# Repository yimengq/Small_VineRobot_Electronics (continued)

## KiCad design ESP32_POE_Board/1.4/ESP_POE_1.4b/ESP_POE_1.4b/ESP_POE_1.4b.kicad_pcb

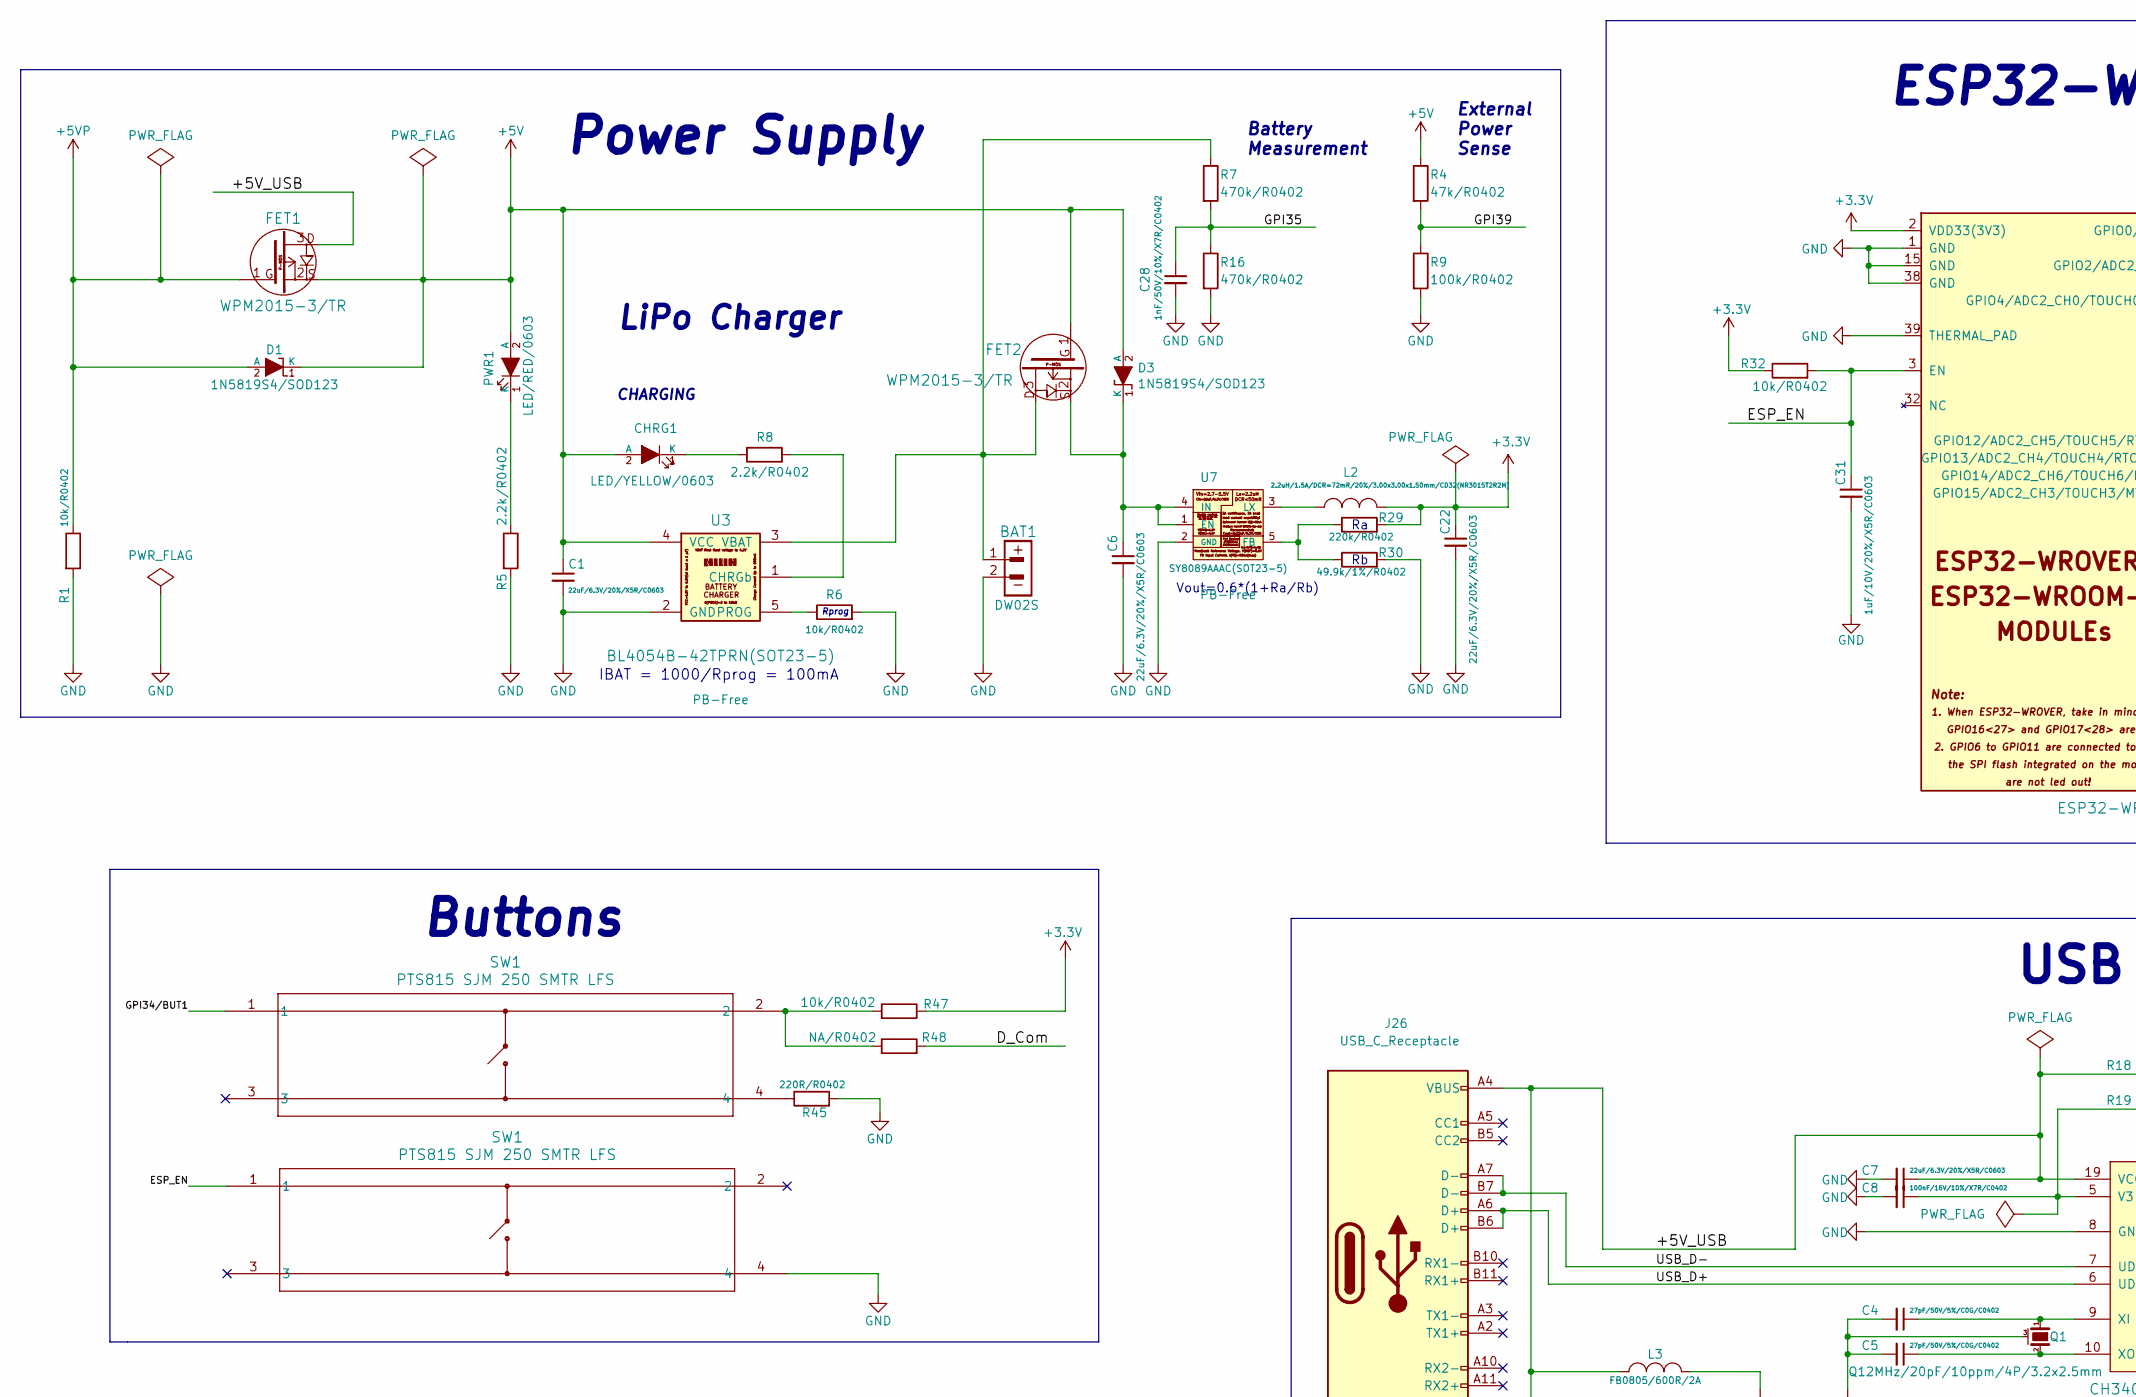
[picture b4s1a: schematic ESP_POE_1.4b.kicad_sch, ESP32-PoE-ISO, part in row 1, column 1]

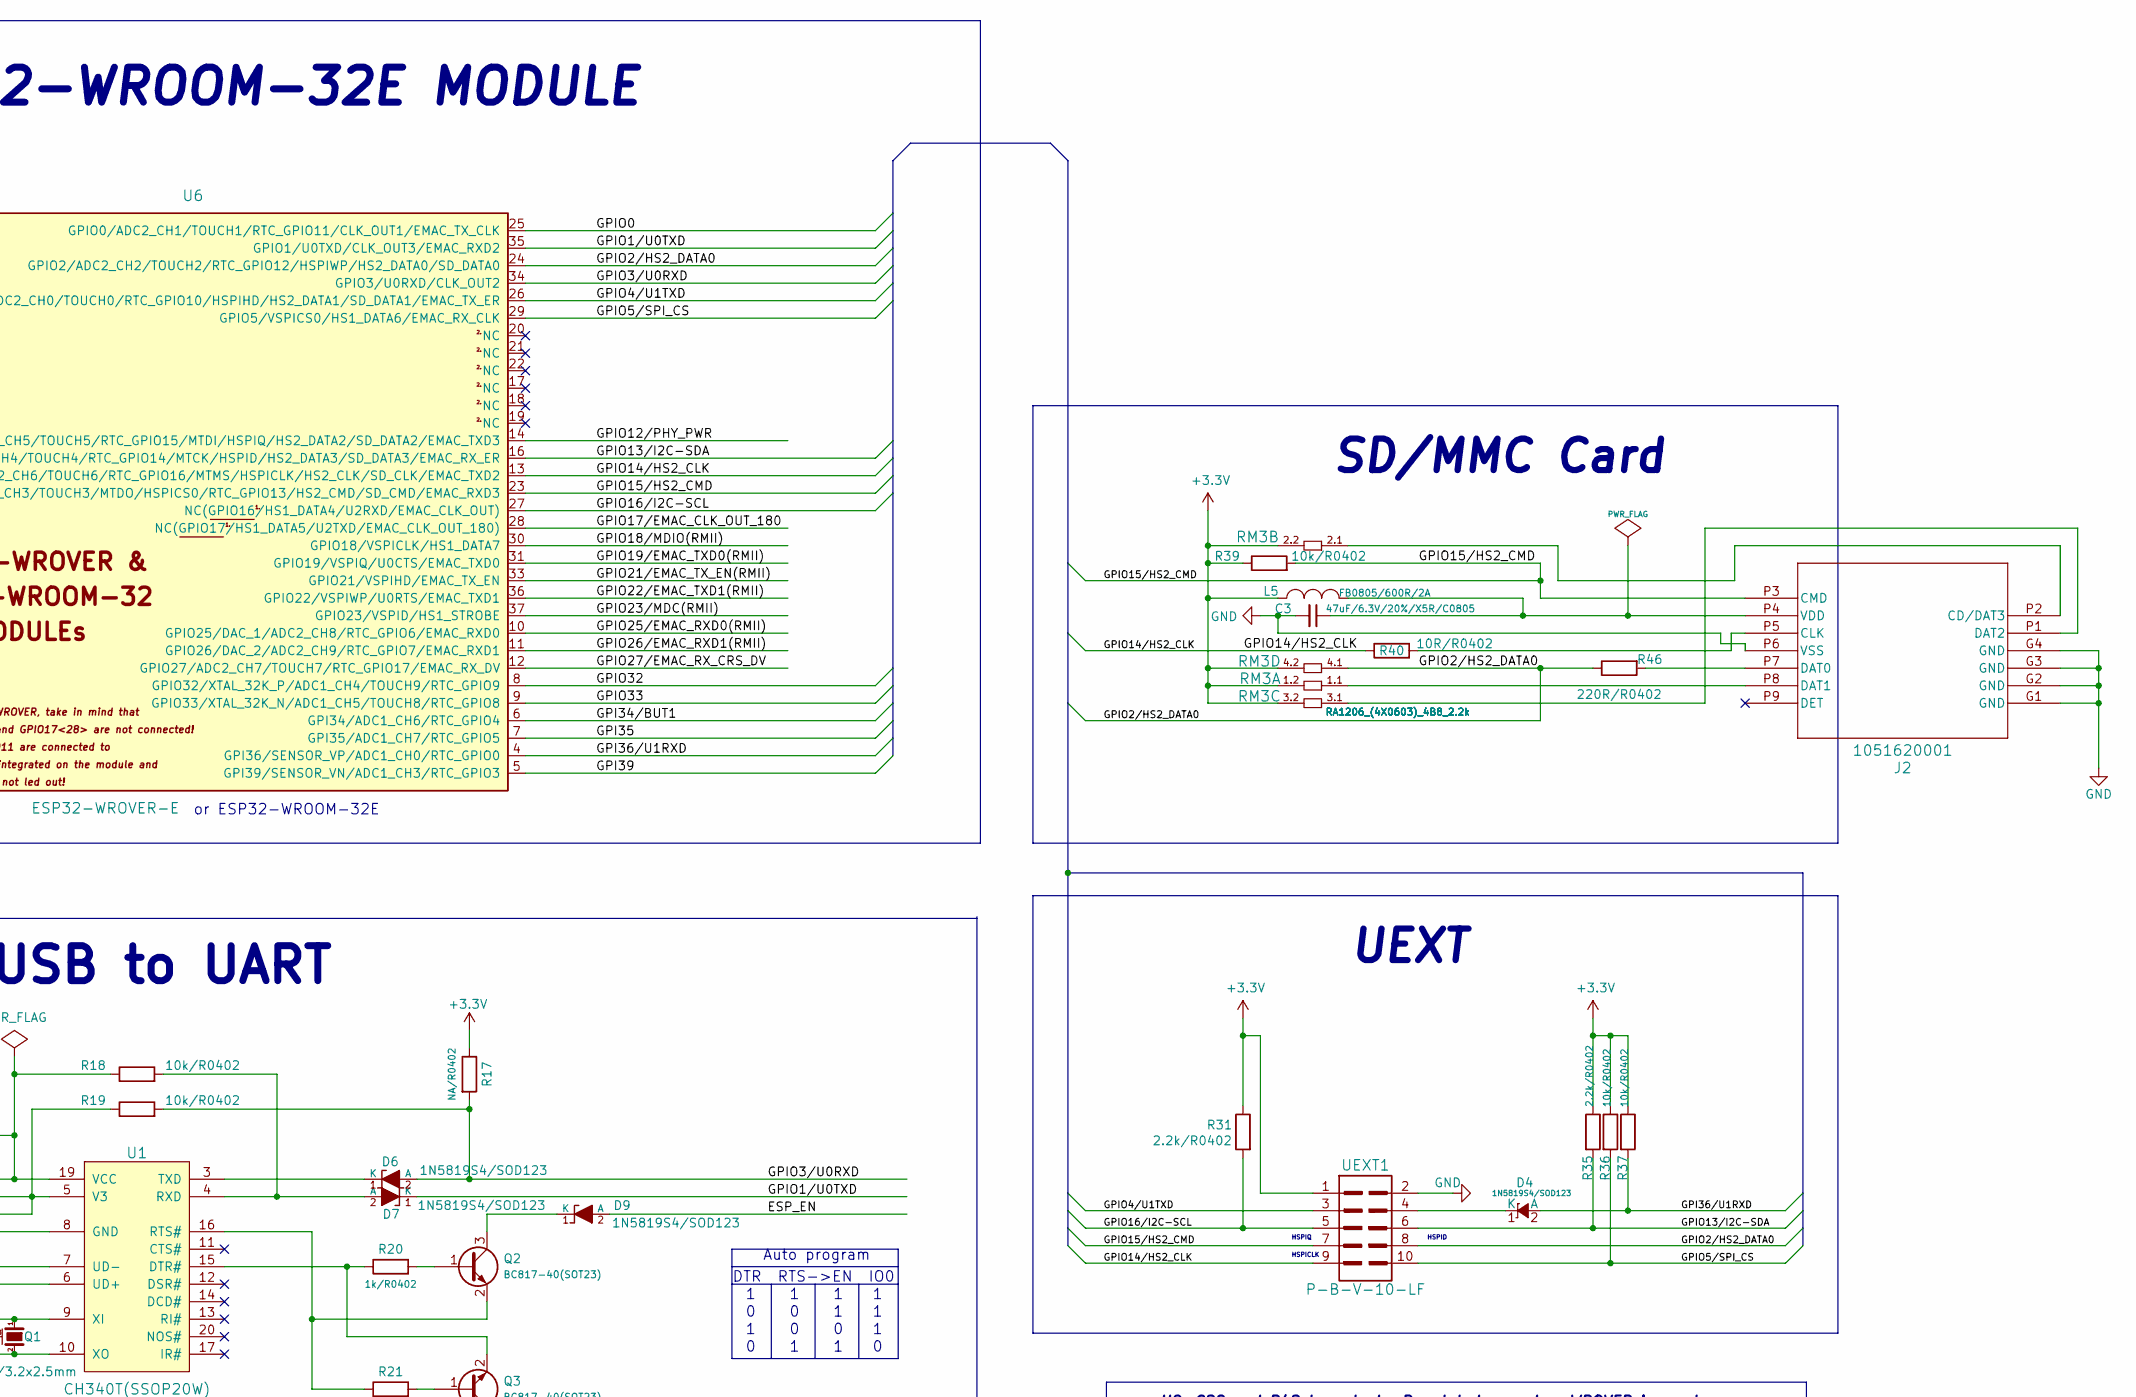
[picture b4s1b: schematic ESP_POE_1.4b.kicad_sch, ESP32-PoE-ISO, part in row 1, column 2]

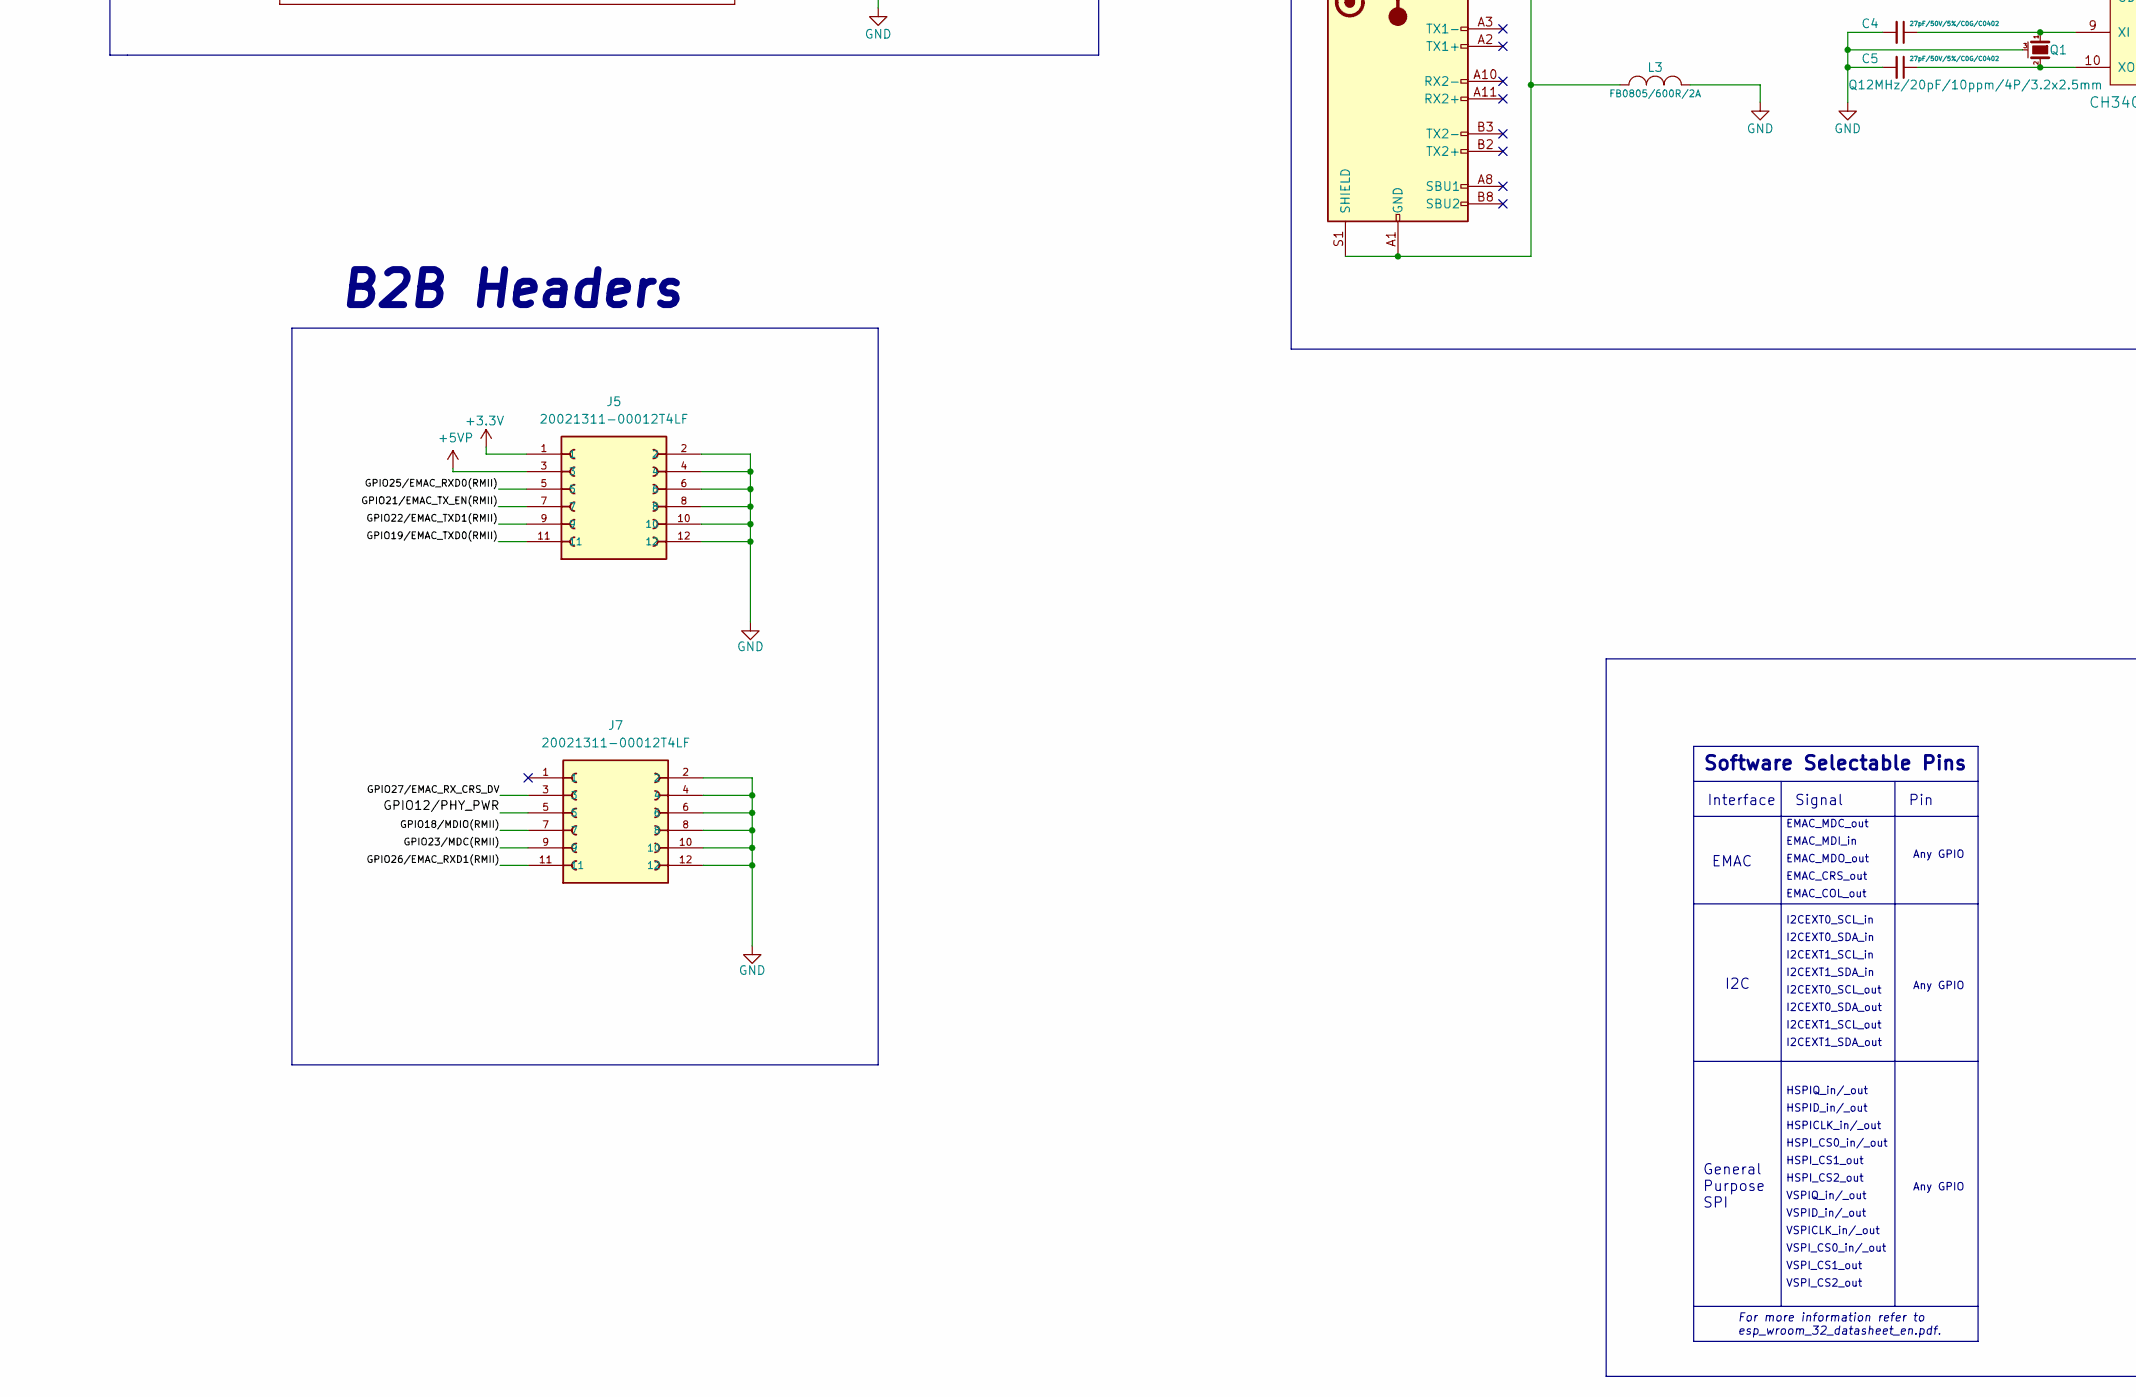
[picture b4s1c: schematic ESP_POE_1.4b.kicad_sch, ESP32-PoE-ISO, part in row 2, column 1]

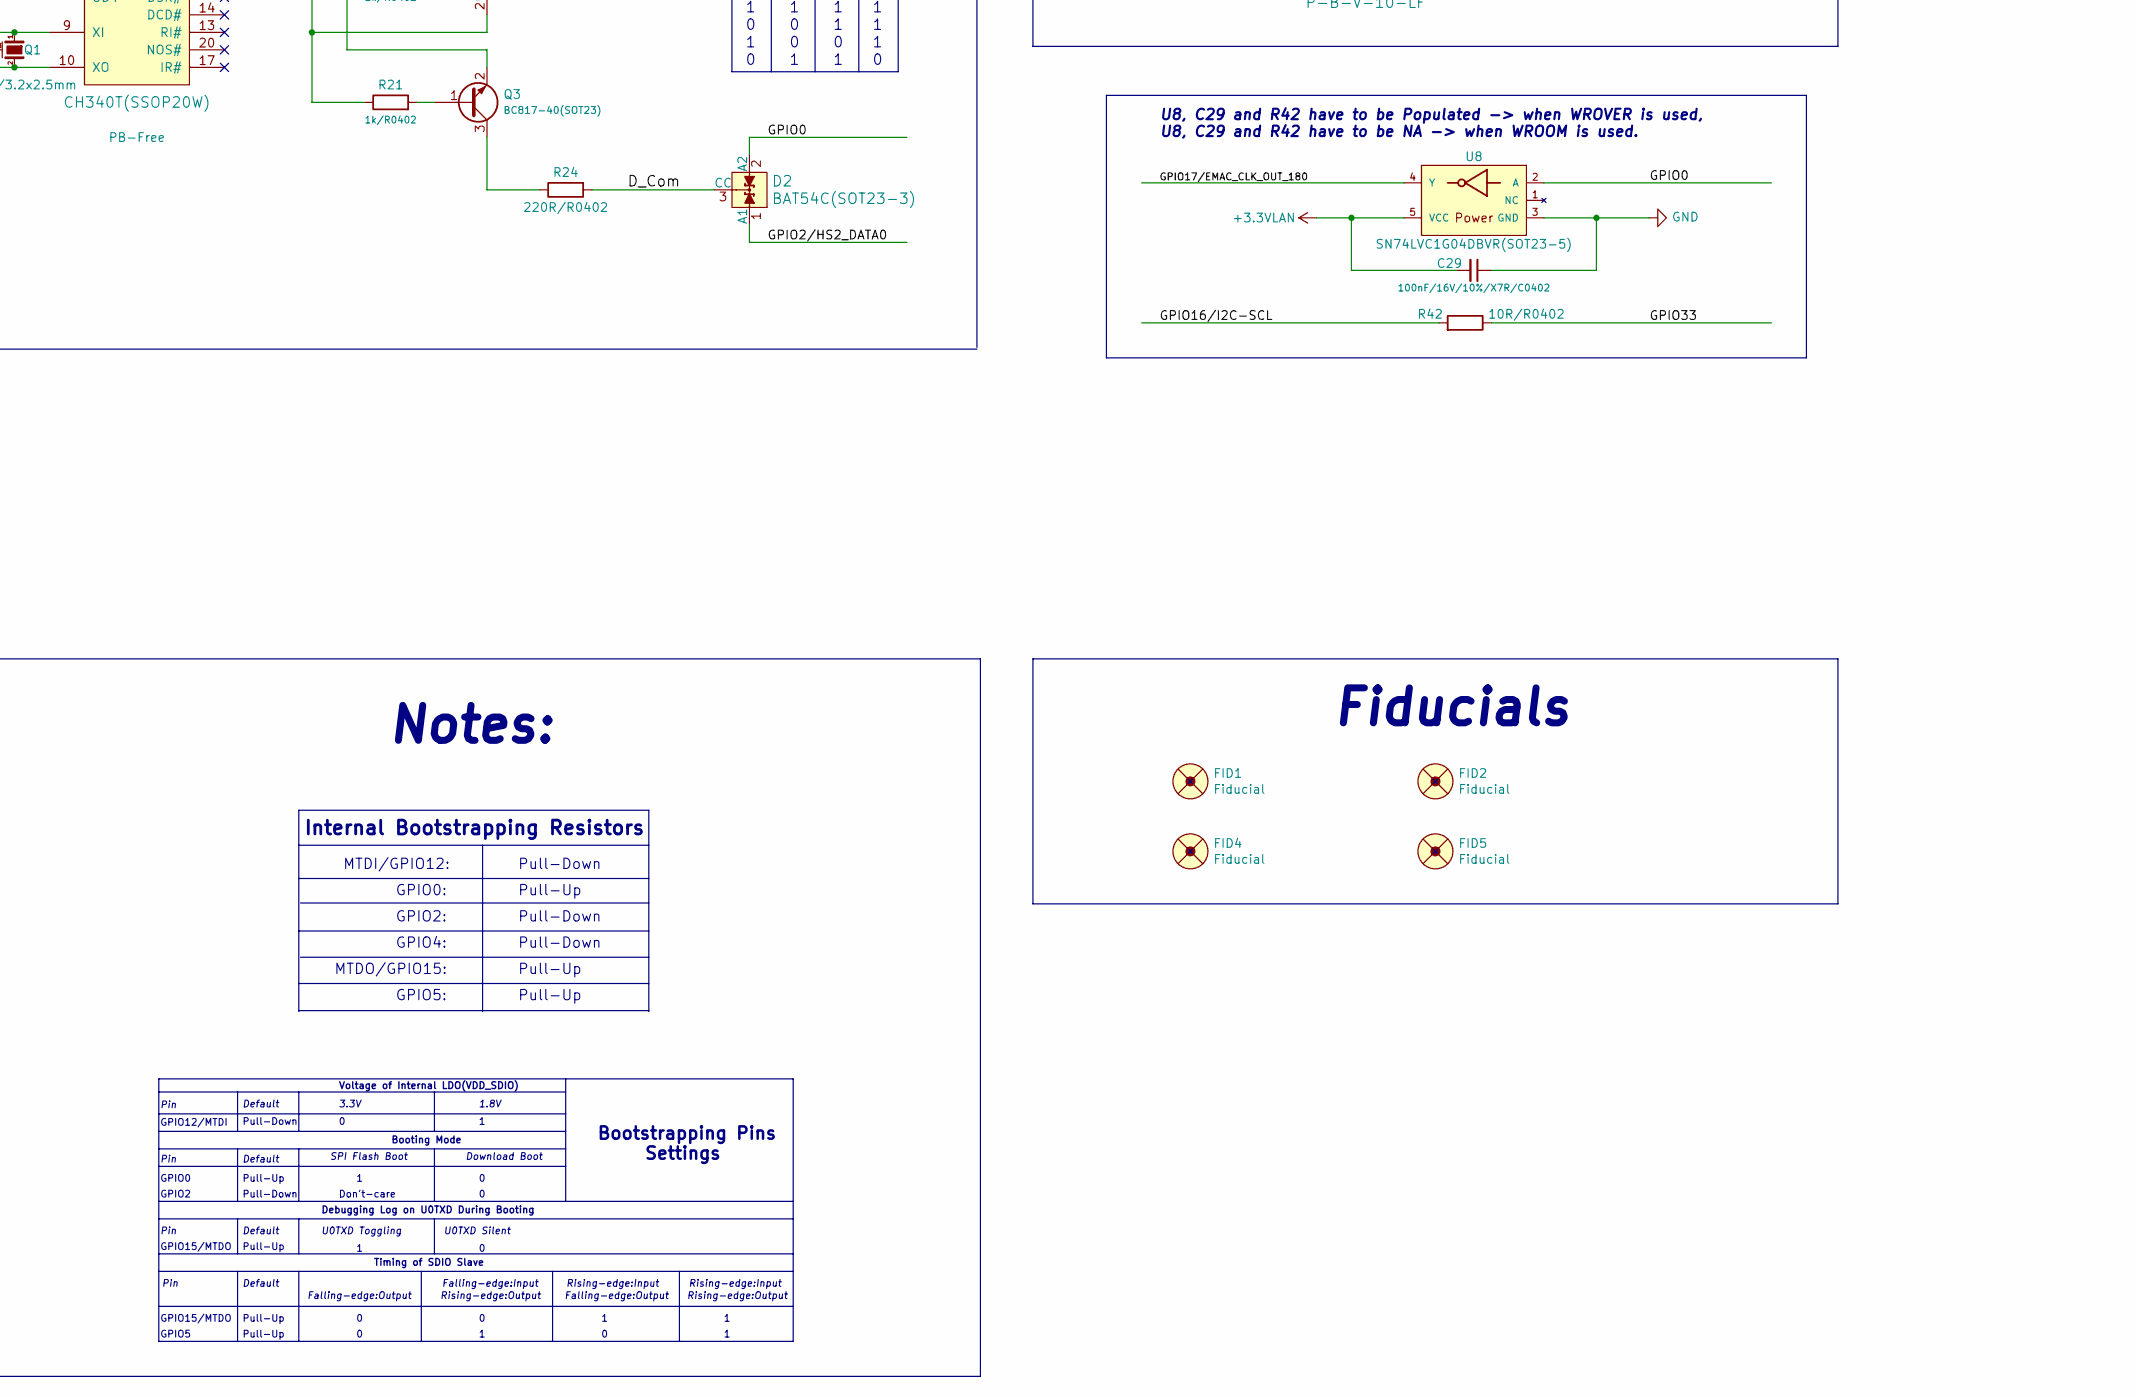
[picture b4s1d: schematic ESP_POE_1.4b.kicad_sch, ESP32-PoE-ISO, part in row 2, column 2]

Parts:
BAT1: DW02S; LIPO_BAT_VERTICAL_DW02S; Mfr P/N DF02S
C1, C6, C7, C22: 22uF/6.3V/20%/X5R/C0603; C_0603_5MIL_DWS; Mfr P/N CL10A226MQ8NRNC
C3: 47uF/6.3V/20%/X5R/C0805; C_0805_5MIL_DWS; Mfr P/N CL21A476MQYNNNE
C4, C5: 27pF/50V/5%/C0G/C0402; C_0402_5MIL_DWS; Mfr P/N CC0402FRNPO9BN270
C8, C29: 100nF/16V/10%/X7R/C0402; C_0402_5MIL_DWS; Mfr P/N CC0402KRX7R7BB104
C28: 1nF/50V/10%/X7R/C0402; C_0402_5MIL_DWS; Mfr P/N CC0402KRX7R9BB102
C31: 1uF/10V/20%/X5R/C0603; C_0603_5MIL_DWS; Mfr P/N CL10B105KP8NNNC
CHRG1: LED/YELLOW/0603; LED_0603_KA; Mfr P/N A-SP192GW1D-D20-4T
D1, D3, D4, D6, D7, D9: 1N5819S4/SOD123; SOD-123_1C-2A_KA; Mfr P/N 1N5819W S4
D2: BAT54C(SOT23-3); SOT23-3; Mfr P/N BAT54C
FET1, FET2: WPM2015-3/TR; SOT23; Mfr P/N WPM2015-3/TR
FID1, FID2, FID4, FID5: Fiducial; Fiducial1x3
J2: 1051620001; 105162-0001_MOL
J5, J7: 20021311-00012T4LF; AMPHENOL_20021311-00012T4LF; Mfr P/N 20021311-00012T4LF
J26: USB_C_Receptacle; USB_C_Receptacle_Molex_105450-0101-L; Mfr P/N 1054500101
L2: 2.2uH/1.5A/DCR=72mR/20%/3.00x3.00x1.50mm/CD32(NR3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; CD32; Mfr P/N ANR3015T2R2M
L3, L5: FB0805/600R/2A; L_0805_5MIL_DWS; Mfr P/N BLM21SP601SZ1D
PWR1: LED/RED/0603; LED_0603_KA; Mfr P/N A-SP194BR5C-C01-3T
Q1: Q12MHz/20pF/10ppm/4P/3.2x2.5mm; TSX-3.2x2.5mm_GND(3); Mfr P/N SX3B12.000F2010F30
Q2, Q3: BC817-40(SOT23); SOT23; Mfr P/N BC817-40,215
R1, R6, R18, R19, R32, R36, R37, R39: 10k/R0402; R_0402_5MIL_DWS; Mfr P/N RC0402FR-0710KL
R4: 47k/R0402; R_0402_5MIL_DWS; Mfr P/N AC0402JR-0747KL
R5, R8, R31, R35: 2.2k/R0402; R_0402_5MIL_DWS; Mfr P/N AC0402JR-072K2L
R7, R16: 470k/R0402; R_0402_5MIL_DWS; Mfr P/N AC0402JR-07470KL
R9: 100k/R0402; R_0402_5MIL_DWS; Mfr P/N RC0402FR-07100KL
R17: NA/R0402; R_0402_5MIL_DWS
R20, R21: 1k/R0402; R_0402_5MIL_DWS; Mfr P/N RC0402FR-071KL
R24, R46: 220R/R0402; R_0402_5MIL_DWS; Mfr P/N CR0402JF0221G
R29: 220k/R0402; R_0402_5MIL_DWS; Mfr P/N RE0402DRE07220KL
R30: 49.9k/1%/R0402; R_0402_5MIL_DWS; Mfr P/N AT0402BRD0749K9L
R40, R42: 10R/R0402; R_0402_5MIL_DWS; Mfr P/N RC0402FR-0710RL
R45: 220R/R0402; R_0402_1005Metric; Mfr P/N CR0402JF0221G
R47: 10k/R0402; R_0402_1005Metric; Mfr P/N RC0402FR-0710KL
R48: NA/R0402; R_0402_1005Metric
RM3: RA1206_(4X0603)_4B8_2.2k; R_MATRIX_4; Mfr P/N 4D03WGJ0222T5E
SW1: PTS815 SJM 250 SMTR LFS; SW4_PTS815 SJM 250 SMTR LFS_CNK; Mfr P/N PTS815SJG250SMTRLFS
U1: CH340T(SSOP20W); SSOP-20W; Mfr P/N CH340T
U3: BL4054B-42TPRN(SOT23-5); SOT-23-5; Mfr P/N BL4054B-42TPRN
U6: ESP32-WROVER-E; ESP32-WROVER(WROOM)-UNIVERSAL_MODULE; Mfr P/N ESP32-WROVER-E-N8R8
U7: SY8089AAAC(SOT23-5); SOT-23-5; Mfr P/N SY8089AAAC
U8: SN74LVC1G04DBVR(SOT23-5); SOT-23-5; Mfr P/N SN74LVC1G04DBVR
UEXT1: P-B-V-10-LF; CONN10_3221-10-0300-00_CNC; Mfr P/N 3221-10-0300-00

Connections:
+3.3VLAN: C29.2, U8.5 (VCC)
+3V3: C22.1, J5.1, L2.2, L5.1, R17.1, R29.2, R31.1, R32.1, R35.1, R36.1, R37.1, R39.1, R47.1, RM3.1.2, RM3.2.2, RM3.3.2, RM3.4.2, U6.2 (VDD33(3V3)), UEXT1.1
+5V: C1.1, CHRG1.2 (A), D1.1 (K), D3.2 (A), FET1.2, FET2.1, PWR1.2 (A), R4.1, U3.4 (VCC)
+5VP: D1.2 (A), FET1.1, J5.3, R1.1
/+5V_USB: C7.1, FET1.3, L3.1, R18.1, U1.19 (VCC); also elsewhere on the board
/D_Com: D2.3 (CC), R24.2, R48.2
/GPI35: C28.1, R7.2, R16.1, U6.7 (GPI35/ADC1_CH7/RTC_GPIO5)
/GPI36/U1RXD: D4.2 (A), R37.2, U6.4 (GPI36/SENSOR_VP/ADC1_CH0/RTC_GPIO0)
/GPI39: R4.2, R9.1, U6.5 (GPI39/SENSOR_VN/ADC1_CH3/RTC_GPIO3)
/GPIO0: D2.2 (A2), U6.25 (GPIO0/ADC2_CH1/TOUCH1/RTC_GPIO11/CLK_OU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), U8.2 (A)
/GPIO1/U0TXD: D7.1 (K), U6.35 (GPIO1/U0TXD/CLK_OUT3/EMAC_RXD2)
/GPIO2/HS2_DATA0: D2.1 (A1), R46.1, RM3.4.1, U6.24 (GPIO2/ADC2_CH2/TOUCH2/RTC_GPIO12/HSPIWP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), UEXT1.8
/GPIO3/U0RXD: D6.2 (A), R17.2, R19.2, U6.34 (GPIO3/U0RXD/CLK_OUT2)
/GPIO4/U1TXD: U6.26 (GPIO4/ADC2_CH0/TOUCH0/RTC_GPIO10/HSPIHD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), UEXT1.3
/GPIO5/SPI_CS: R36.2, U6.29 (GPIO5/VSPICS0/HS1_DATA6/EMAC_RX_CLK), UEXT1.10
/GPIO12/PHY_PWR: J7.5, U6.14 (GPIO12/ADC2_CH5/TOUCH5/RTC_GPIO15/MTDI/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)
/GPIO13/I2C-SDA: R35.2, U6.16 (GPIO13/ADC2_CH4/TOUCH4/RTC_GPIO14/MTCK/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), UEXT1.6
/GPIO14/HS2_CLK: R40.1, U6.13 (GPIO14/ADC2_CH6/TOUCH6/RTC_GPIO16/MTMS/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), UEXT1.9
/GPIO15/HS2_CMD: J2.P3 (CMD), R39.2, U6.23 (GPIO15/ADC2_CH3/TOUCH3/MTDO/HSPICS0/RTC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), UEXT1.7
/GPIO16/I2C-SCL: R31.2, R42.2, U6.27 (NC(GPIO16/HS1_DATA4/U2RXD/EMAC_CLK_OUT)), UEXT1.5
/GPIO17/EMAC_CLK_OUT_180: U6.28 (NC(GPIO17/HS1_DATA5/U2TXD/EMAC_CLK_OUT_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), U8.4 (Y)
/GPIO18/MDIO(RMII): J7.7, U6.30 (GPIO18/VSPICLK/HS1_DATA7)
/GPIO19/EMAC_TXD0(RMII): J5.11, U6.31 (GPIO19/VSPIQ/U0CTS/EMAC_TXD0)
/GPIO21/EMAC_TX_EN(RMII): J5.7, U6.33 (GPIO21/VSPIHD/EMAC_TX_EN)
/GPIO22/EMAC_TXD1(RMII): J5.9, U6.36 (GPIO22/VSPIWP/U0RTS/EMAC_TXD1)
/GPIO23/MDC(RMII): J7.9, U6.37 (GPIO23/VSPID/HS1_STROBE)
/GPIO25/EMAC_RXD0(RMII): J5.5, U6.10 (GPIO25/DAC_1/ADC2_CH8/RTC_GPIO6/EMAC_RX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)
/GPIO26/EMAC_RXD1(RMII): J7.11, U6.11 (GPIO26/DAC_2/ADC2_CH9/RTC_GPIO7/EMAC_RX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)
/GPIO27/EMAC_RX_CRS_DV: J7.3, U6.12 (GPIO27/ADC2_CH7/TOUCH7/RTC_GPIO17/EMAC_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)
/GPIO32: U6.8 (GPIO32/XTAL_32K_P/ADC1_CH4/TOUCH9/RTC_G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)
/GPIO33: R42.1, U6.9 (GPIO33/XTAL_32K_N/ADC1_CH5/TOUCH8/RTC_G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)
/USB_D+: U1.6 (UD+); also elsewhere on the board
/USB_D-: U1.7 (UD-); also elsewhere on the board
unnamed: CHRG1.1 (K), R8.1
unnamed: C6.1, D3.1 (K), FET2.2, U7.1 (EN), U7.4 (IN)
unnamed: D4.1 (K), UEXT1.4
unnamed: D6.1 (K), U1.3 (TXD)
unnamed: D7.2 (A), R18.2, U1.4 (RXD)
unnamed: D9.1 (K), Q2.3 (C)
unnamed: J2.P2 (CD/DAT3), RM3.2.1
unnamed: J2.P5 (CLK), R40.2
unnamed: J2.P7 (DAT0), R46.2
unnamed: J2.P8 (DAT1), RM3.1.1
unnamed: J2.P1 (DAT2), RM3.3.1
unnamed: C3.1, J2.P4 (VDD), L5.2
unnamed: PWR1.1 (K), R5.1
unnamed: Q2.1 (B), R20.2
unnamed: Q2.2 (E), R21.1, U1.16 (RTS#)
unnamed: Q3.1 (B), R21.2
unnamed: Q3.3 (C), R24.1
unnamed: Q3.2 (E), R20.1, U1.15 (DTR#)
unnamed: R47.2, R48.1, SW1.2
unnamed: C8.1, R19.1, U1.5 (V3)
unnamed: C4.1, Q1.1, U1.9 (XI)
unnamed: C5.1, Q1.2, U1.10 (XO)
unnamed: R8.2, U3.1 (CHRGb)
unnamed: R6.1, U3.5 (PROG)
unnamed: BAT1.1, FET2.3, R7.1, U3.3 (VBAT)
unnamed: R29.1, R30.1, U7.5 (FB)
unnamed: L2.1, U7.3 (LX)

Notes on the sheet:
I2CEXT0_SCL_out
EMAC_MDI_in
HSPIQ
Default
HSPID_in/_out
EMAC
VSPI_CS1_out
EMAC_MDO_out
U0TXD Toggling
I2CEXT1_SCL_out
GPIO5:
ESP32-WROOM-32E MODULE
MTDO/GPIO15:
HSPI_CS2_out
Battery Measurement
HSPI_CS0_in/_out
MTDI/GPIO12:
Pin
Vout=0.6*(1+Ra/Rb)
Rising-edge:Output
Rprog
I2CEXT0_SCL_in
Any GPIO
Falling-edge:Input
Booting Mode
B2B Headers
GPIO15/MTDO
U0TXD Silent
Rising-edge:Input
Pull-Up
I2C
Auto program
VSPIQ_in/_out
General Purpose SPI
Falling-edge:Output
Signal
Pull-Down
Power Supply
IBAT = 1000/Rprog = 100mA
UEXT

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
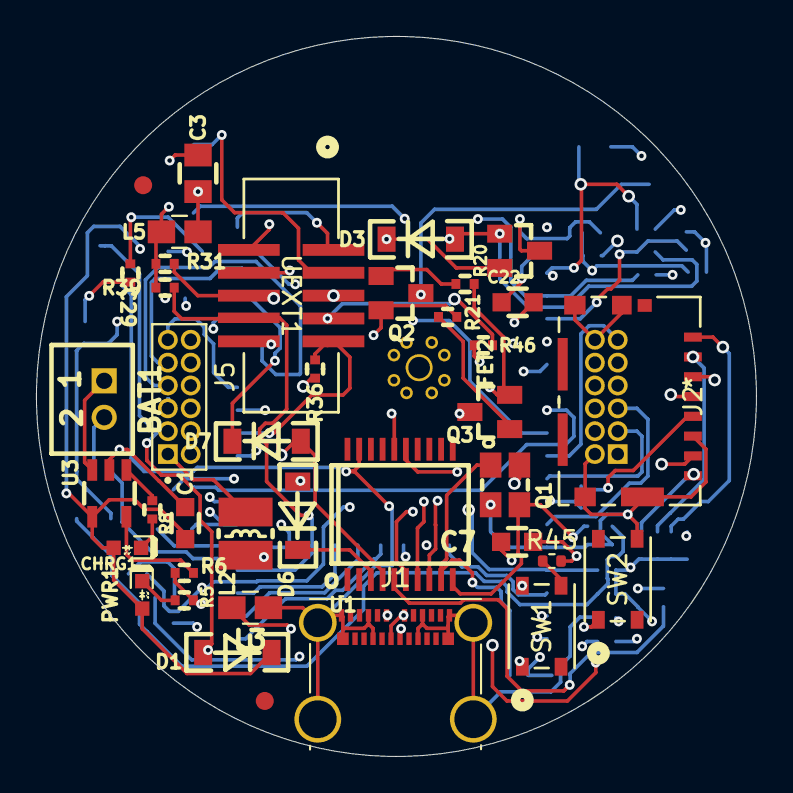
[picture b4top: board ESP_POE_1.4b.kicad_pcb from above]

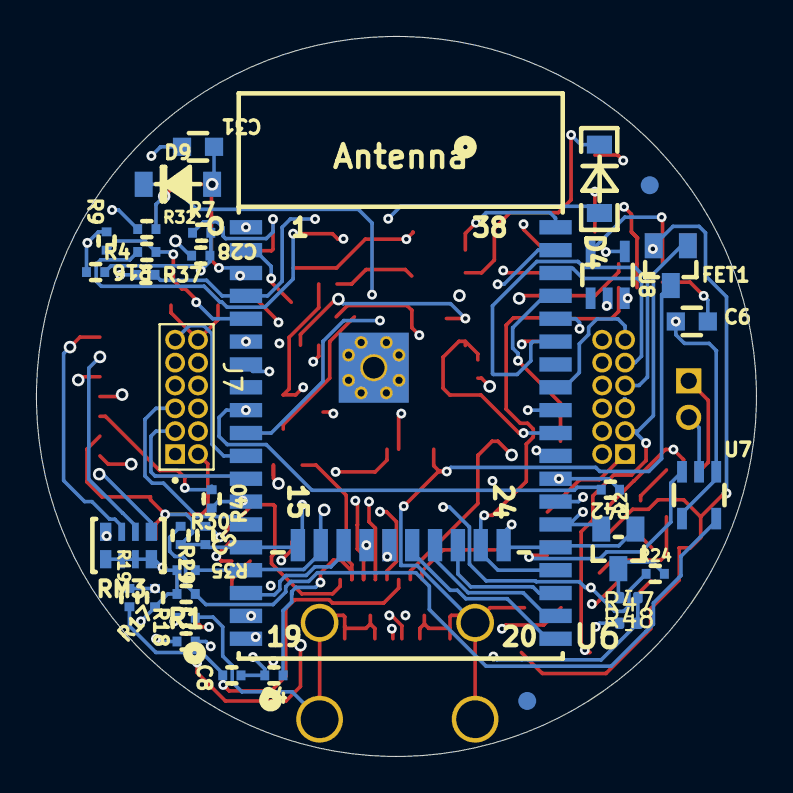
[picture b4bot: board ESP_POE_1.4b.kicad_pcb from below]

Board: 6 copper layers, 40.0 x 40.0 mm, 74 parts (35 on the bottom side), 63 nets.

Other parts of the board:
J1: USB_C_Receptacle; USB_C_Receptacle_Molex_105450-0101-L
SW2: PTS815 SJM 250 SMTR LFS; SW4_PTS815 SJM 250 SMTR LFS_CNK

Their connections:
/+5V_USB: J1.A1 (GND), J1.A4 (VBUS), J1.A9 (VBUS), J1.A12 (GND), J1.B1 (GND), J1.B4 (VBUS), J1.B9 (VBUS), J1.B12 (GND), J1.S1 (SHIELD); also elsewhere on the board
/USB_D+: J1.A6 (D+), J1.B6 (D+); also elsewhere on the board
/USB_D-: J1.A7 (D-), J1.B7 (D-); also elsewhere on the board

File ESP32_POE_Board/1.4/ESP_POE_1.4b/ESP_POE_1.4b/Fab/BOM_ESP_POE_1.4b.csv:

"Reference","Value","Footprint","Datasheet","Mfr","Mfr P/N","Note","Supplier 1","Supplier 1 P/N","price","purchase url","Qty"
"BAT1","DW02S","OLIMEX_Connectors-FP:LIPO_BAT_VERTICAL_DW02S","","Diodes Incorporated","DF02S","","LCSC","C151398","0.2519","https://www.lcsc.com/product-detail/Bridge-Rectifiers_Diodes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","1"
"C1, C6, C7, C22","22uF/6.3V/20%/X5R/C0603","OLIMEX_RLC-FP:C_0603_5MIL_DWS","","Samsung Electro-Mechanics","CL10A226MQ8NRNC","","LCSC","C59461","0.0078","https://www.lcsc.com/product-detail/Multilayer-Ceramic-Capac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","4"
"C3","47uF/6.3V/20%/X5R/C0805","OLIMEX_RLC-FP:C_0805_5MIL_DWS","","Samsung Electro-Mechanics","CL21A476MQYNNNE","","LCSC","C16780","0.0212","https://www.lcsc.com/product-detail/Multilayer-Ceramic-Capac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","1"
"C4, C5","27pF/50V/5%/C0G/C0402","OLIMEX_RLC-FP:C_0402_5MIL_DWS","","YAGEO","CC0402FRNPO9BN270","","LCSC","C277506","0.0031","https://www.lcsc.com/product-detail/Multilayer-Ceramic-Capac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","2"
"C8, C29","100nF/16V/10%/X7R/C0402","OLIMEX_RLC-FP:C_0402_5MIL_DWS","","YAGEO","CC0402KRX7R7BB104","","LCSC","C60474","","https://www.lcsc.com/product-detail/Multilayer-Ceramic-Capac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","2"
"C28","1nF/50V/10%/X7R/C0402","OLIMEX_RLC-FP:C_0402_5MIL_DWS","","YAGEO","CC0402KRX7R9BB102","","LCSC","C106205","0.0008","https://www.lcsc.com/product-detail/Multilayer-Ceramic-Capac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","1"
"C31","1uF/10V/20%/X5R/C0603","OLIMEX_RLC-FP:C_0603_5MIL_DWS","","Samsung Electro-Mechanics","CL10B105KP8NNNC","","LCSC","C95843","0.0046","https://www.lcsc.com/product-detail/Multilayer-Ceramic-Capac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","1"
"CHRG1","LED/YELLOW/0603","OLIMEX_LEDs-FP:LED_0603_KA","","Amicc","A-SP192GW1D-D20-4T","","LCSC","C5179600","0.0205","https://www.lcsc.com/product-detail/span-style-background-co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","1"
"D1, D3, D4, D6, D7, D9","1N5819S4/SOD123","OLIMEX_Diodes-FP:SOD-123_1C-2A_KA","","KUU","1N5819W S4","","LCSC","C2939006","0.0079","https://www.lcsc.com/product-detail/Schottky-Diodes_KUU-1N58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","6"
"D2","BAT54C(SOT23-3)","OLIMEX_Diodes-FP:SOT23-3","","Slkor","BAT54C","","LCSC","C556168","0.0120","https://www.lcsc.com/product-detail/Schottky-Diodes_Slkor-SL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","1"
"FET1, FET2","WPM2015-3/TR","OLIMEX_Transistors-FP:SOT23","","KUU","WPM2015-3/TR","","LCSC","C6562215","0.0362","https://www.lcsc.com/product-detail/MOSFETs_KUU-WPM2015-3-TR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","2"
"FID1, FID2, FID4, FID5","Fiducial","OLIMEX_Other-FP:Fiducial1x3","","","","","","","","","4"
"J1","USB_C_Receptacle","Connector_USB:USB_C_Receptacle_Molex_105450-0101-L","https://www.usb.org/sites/default/files/documents/usb_type-c.zip","MOLEX","1054500101","","LCSC","C134092","0.9231","https://www.lcsc.com/product-detail/USB-Connectors_MOLEX-105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","1"
"J5, J7","20021311-00012T4LF","20021311-00012T4LF:AMPHENOL_20021311-00012T4LF","","Amphenol ICC","20021311-00012T4LF","","LCSC","C3319562","1.1062","https://www.lcsc.com/product-detail/Female-Headers_Amphenol-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","2"
"L2","2.2uH/1.5A/DCR=72mR/20%/3.00x3.00x1.50mm/CD32(NR3015T2R2M)","OLIMEX_RLC-FP:CD32","","APV","ANR3015T2R2M","","LCSC","C6364793","0.0309","https://www.lcsc.com/product-detail/Power-Inductors_APV-ANR3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","1"
"L3, L5","FB0805/600R/2A","OLIMEX_RLC-FP:L_0805_5MIL_DWS","","Murata Electronics","BLM21SP601SZ1D","","LCSC","C2661781","0.2178","https://www.lcsc.com/product-detail/Ferrite-Beads_Murata-Ele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","2"
"MICRO_SD1","TFC-9P-1.7H(ATFFS150A01BR016)","OLIMEX_Connectors-FP:uSD(TFC-9P-1.xH(ATFFS150A01BR016))","http://www.globalsources.com/gsol/I/Memory-card/p/sm/1148705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","Molex","1051620001","solder later","Digikey","WM14405CT-ND","0.99000","https://www.digikey.com/en/products/detail/molex/1051620001/4555282","1"
"PWR1","LED/RED/0603","OLIMEX_LEDs-FP:LED_0603_KA","","Amicc","A-SP194BR5C-C01-3T","","LCSC","C2760778","0.0173","https://www.lcsc.com/product-detail/span-style-background-co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","1"
"Q1","Q12MHz/20pF/10ppm/4P/3.2x2.5mm","OLIMEX_Crystal-FP:TSX-3.2x2.5mm_GND(3)","","Shenzhen SCTF Elec","SX3B12.000F2010F30","","LCSC","C2901652","0.0600","https://www.lcsc.com/product-detail/Crystals_Shenzhen-SCTF-E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","1"
"Q2, Q3","BC817-40(SOT23)","OLIMEX_Transistors-FP:SOT23","","Nexperia","BC817-40,215","","LCSC","C52801","0.0099","https://www.lcsc.com/product-detail/Bipolar-BJT_Nexperia-BC8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","2"
"R1, R6, R18, R19, R32, R36, R37, R39, R47","10k/R0402","OLIMEX_RLC-FP:R_0402_5MIL_DWS","","YAGEO","RC0402FR-0710KL","","LCSC","C60490","","https://www.lcsc.com/product-detail/Chip-span-style-backgrou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","9"
"R4","47k/R0402","OLIMEX_RLC-FP:R_0402_5MIL_DWS","","YAGEO","AC0402JR-0747KL","","LCSC","C144710","0.0009","https://www.lcsc.com/product-detail/Chip-span-style-backgrou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","1"
"R5, R8, R31, R35","2.2k/R0402","OLIMEX_RLC-FP:R_0402_5MIL_DWS","","YAGEO","AC0402JR-072K2L","","LCSC","C144718","0.0008","https://www.lcsc.com/product-detail/Chip-span-style-backgrou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","4"
"R7, R16","470k/R0402","OLIMEX_RLC-FP:R_0402_5MIL_DWS","","YAGEO","AC0402JR-07470KL","","LCSC","C227380","0.0005","https://www.lcsc.com/product-detail/Chip-span-style-backgrou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","2"
"R9","100k/R0402","OLIMEX_RLC-FP:R_0402_5MIL_DWS","","YAGEO","RC0402FR-07100KL","","LCSC","C60491","","https://www.lcsc.com/product-detail/Chip-span-style-backgrou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","1"
"R17, R48","NA/R0402","OLIMEX_RLC-FP:R_0402_5MIL_DWS","","","","","","","","","2"
"R20, R21","1k/R0402","OLIMEX_RLC-FP:R_0402_5MIL_DWS","","YAGEO","RC0402FR-071KL","","LCSC","C106235","0.0006","https://www.lcsc.com/product-detail/Chip-span-style-backgrou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","2"
"R24, R45, R46","220R/R0402","OLIMEX_RLC-FP:R_0402_5MIL_DWS","","LIZ Elec","CR0402JF0221G","","LCSC","C100613","0.0004","https://www.lcsc.com/product-detail/Chip-Resistor-Surface-Mo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","3"
"R29","220k/R0402","OLIMEX_RLC-FP:R_0402_5MIL_DWS","","YAGEO","RE0402DRE07220KL","","LCSC","C851925","0.0031","https://www.lcsc.com/product-detail/Chip-span-style-backgrou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","1"
"R30","49.9k/1%/R0402","OLIMEX_RLC-FP:R_0402_5MIL_DWS","","YAGEO","AT0402BRD0749K9L","","LCSC","C851029","0.0448","https://www.lcsc.com/product-detail/Chip-span-style-backgrou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","1"
"R40, R42","10R/R0402","OLIMEX_RLC-FP:R_0402_5MIL_DWS","","YAGEO","RC0402FR-0710RL","","LCSC","C138066"," 0.0014","https://www.lcsc.com/product-detail/Chip-span-style-backgrou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","2"
"RM3","RA1206_(4X0603)_4B8_2.2k","OLIMEX_RLC-FP:R_MATRIX_4","","UNI-ROYAL(Uniroyal Elec)","4D03WGJ0222T5E","","LCSC","C12001","0.0049","https://www.lcsc.com/product-detail/Resistor-Networks-Arrays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","1"
"SW1, SW2","PTS815 SJM 250 SMTR LFS","SW4_PTS815 SJM 250 SMTR LFS_CNK","PTS815 SJM 250 SMTR LFS","C&K","PTS815SJG250SMTRLFS","","LCSC","C411883","0.0850","https://www.lcsc.com/product-detail/Tactile-Switches_C-K-PTS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","2"
"U1","CH340T(SSOP20W)","OLIMEX_IC-FP:SSOP-20W","","WCH(Jiangsu Qin Heng)","CH340T","PB-Free","LCSC","C8689","0.6253","https://www.lcsc.com/product-detail/USB-Converters_WCH-Jiang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","1"
"U3","BL4054B-42TPRN(SOT23-5)","OLIMEX_IC-FP:SOT-23-5","https://datasheet.lcsc.com/szlcsc/BL4054B-42TPRN_C83783.pdf","BL(Shanghai Belling)","BL4054B-42TPRN","PB-Free","LCSC","C83783"," 0.1470","https://www.lcsc.com/product-detail/Battery-Management_BL-Sh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","1"
"U6","ESP32-WROVER-E","OLIMEX_Cases-FP:ESP32-WROVER(WROOM)-UNIVERSAL_MODULE","","Espressif Systems","ESP32-WROVER-E-N8R8","","LCSC","C2973667","4.6460","https://www.lcsc.com/product-detail/WiFi-Modules_Espressif-S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","1"
"U7","SY8089AAAC(SOT23-5)","OLIMEX_Regulators-FP:SOT-23-5","","Silergy Corp","SY8089AAAC","PB-Free","LCSC","C78988","0.1537","https://www.lcsc.com/product-detail/DC-DC-Converters_Silergy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","1"
"U8","SN74LVC1G04DBVR(SOT23-5)","OLIMEX_IC-FP:SOT-23-5","","Texas Instruments","SN74LVC1G04DBVR","","LCSC","C7827","0.0520","https://www.lcsc.com/product-detail/Inverters_Texas-Instrume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","1"
"UEXT1","P-B-V-10-LF","3221-10-0300-00:CONN10_3221-10-0300-00_CNC","","CNC Tech","3221-10-0300-00","Solder later","Digikey","1175-1735-ND","1.02000","https://www.digikey.com/en/products/detail/cnc-tech/3221-10-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","1"
